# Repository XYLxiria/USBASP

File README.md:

# USBASP
<head>USBASP AVR InSytemProgramer (ISP).</head>
<br>Based on original USBasp from Thomas Fischl.
<br>I used KiCAD for designing schematics and PCB.

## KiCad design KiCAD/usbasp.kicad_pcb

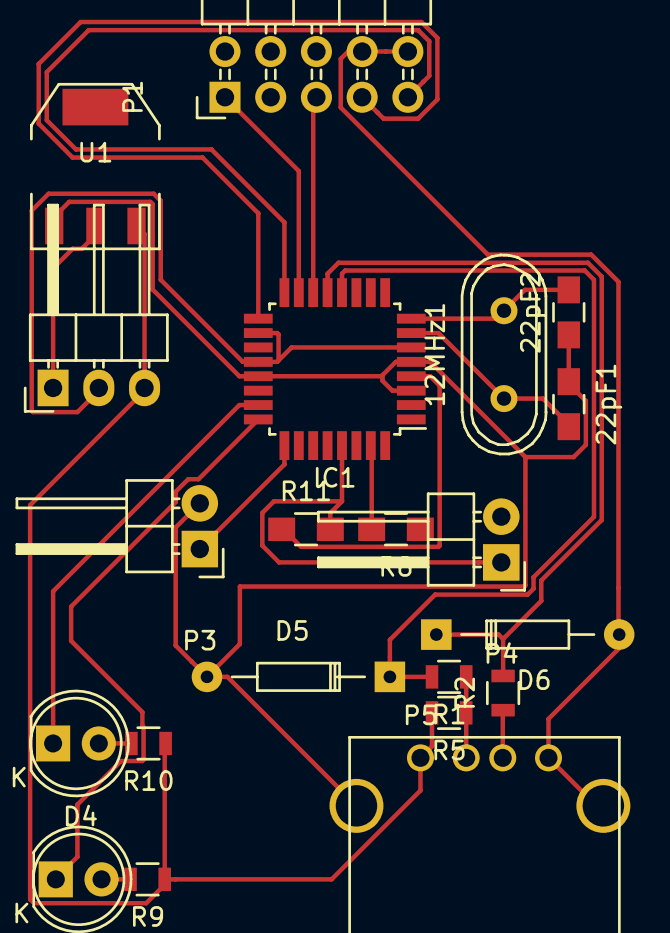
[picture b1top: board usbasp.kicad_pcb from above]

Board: 2 copper layers, 21 parts (0 on the bottom side), 23 nets.

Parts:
12MHz1: Crystal; Crystal_HC49-U_Vertical
22pF1: C1; C_0805_HandSoldering
22pF2: C2; C_0805_HandSoldering
D3: LED_GREEN; LED-5MM
D4: LED_RED; LED-5MM
D5, D6: ZENERsmall; Diode_DO-35_SOD27_Horizontal_RM10
IC1: ATMEGA88-A; TQFP-32_7x7mm_Pitch0.8mm
P1: ISP; Pin_Header_Angled_2x05
P2: VoltageSelect; Pin_Header_Angled_1x03
P3: SlowCLK; Pin_Header_Angled_1x02
P4: SelfPrograming; Pin_Header_Angled_1x02
P5: USB_B; USB_A
R1, R2: 68; R_0805
R5: 2K2; R_0805
R8, R11: 1K; R_0805_HandSoldering
R9, R10: 1K; R_0805
U1: AP1117; SOT-223

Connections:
+5V: P2.3, P5.1, R5.2, R9.1, R10.1, U1.3
GND: 22pF1.1, 22pF2.1, D5.2, D6.2, IC1.3, IC1.5, IC1.21, P1.3, P1.8, P1.10, P3.2, P5.4, P5.5, U1.1
LED1: D3.1, IC1.24
LED2: D4.1, IC1.23
MISO: IC1.16, P1.9
MOSI: IC1.15, P1.1
unnamed: D3.2, R9.2
unnamed: D4.2, R10.2
unnamed: IC1.31, R8.2
unnamed: P2.1, U1.2
unnamed: P5.2, R1.1, R5.1
unnamed: P5.3, R2.1
RST_SS: IC1.14, P1.5, P4.2
RXD: IC1.30, P1.6
Reset: IC1.29, P4.1, R11.2
SCK: IC1.17, P1.7
SlowCLK: IC1.25, P3.1
TXD: P1.4, R8.1
USB_D+: D6.1, IC1.13, R2.2
USB_D-: D5.1, IC1.12, R1.2
VCC: IC1.4, IC1.6, IC1.18, IC1.20, P1.2, P2.2, R11.1
XTAL1: 12MHz1.1, 22pF1.2, IC1.7
XTAL2: 12MHz1.2, 22pF2.2, IC1.8

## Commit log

2015-08-03 PCB layout WiP
2015-08-04 Plotter specific PCB added
